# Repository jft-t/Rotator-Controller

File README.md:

# Rotator-Controller
Rotator Controller for SPID BigRAS rotator, suited for use within SatNOGS stations

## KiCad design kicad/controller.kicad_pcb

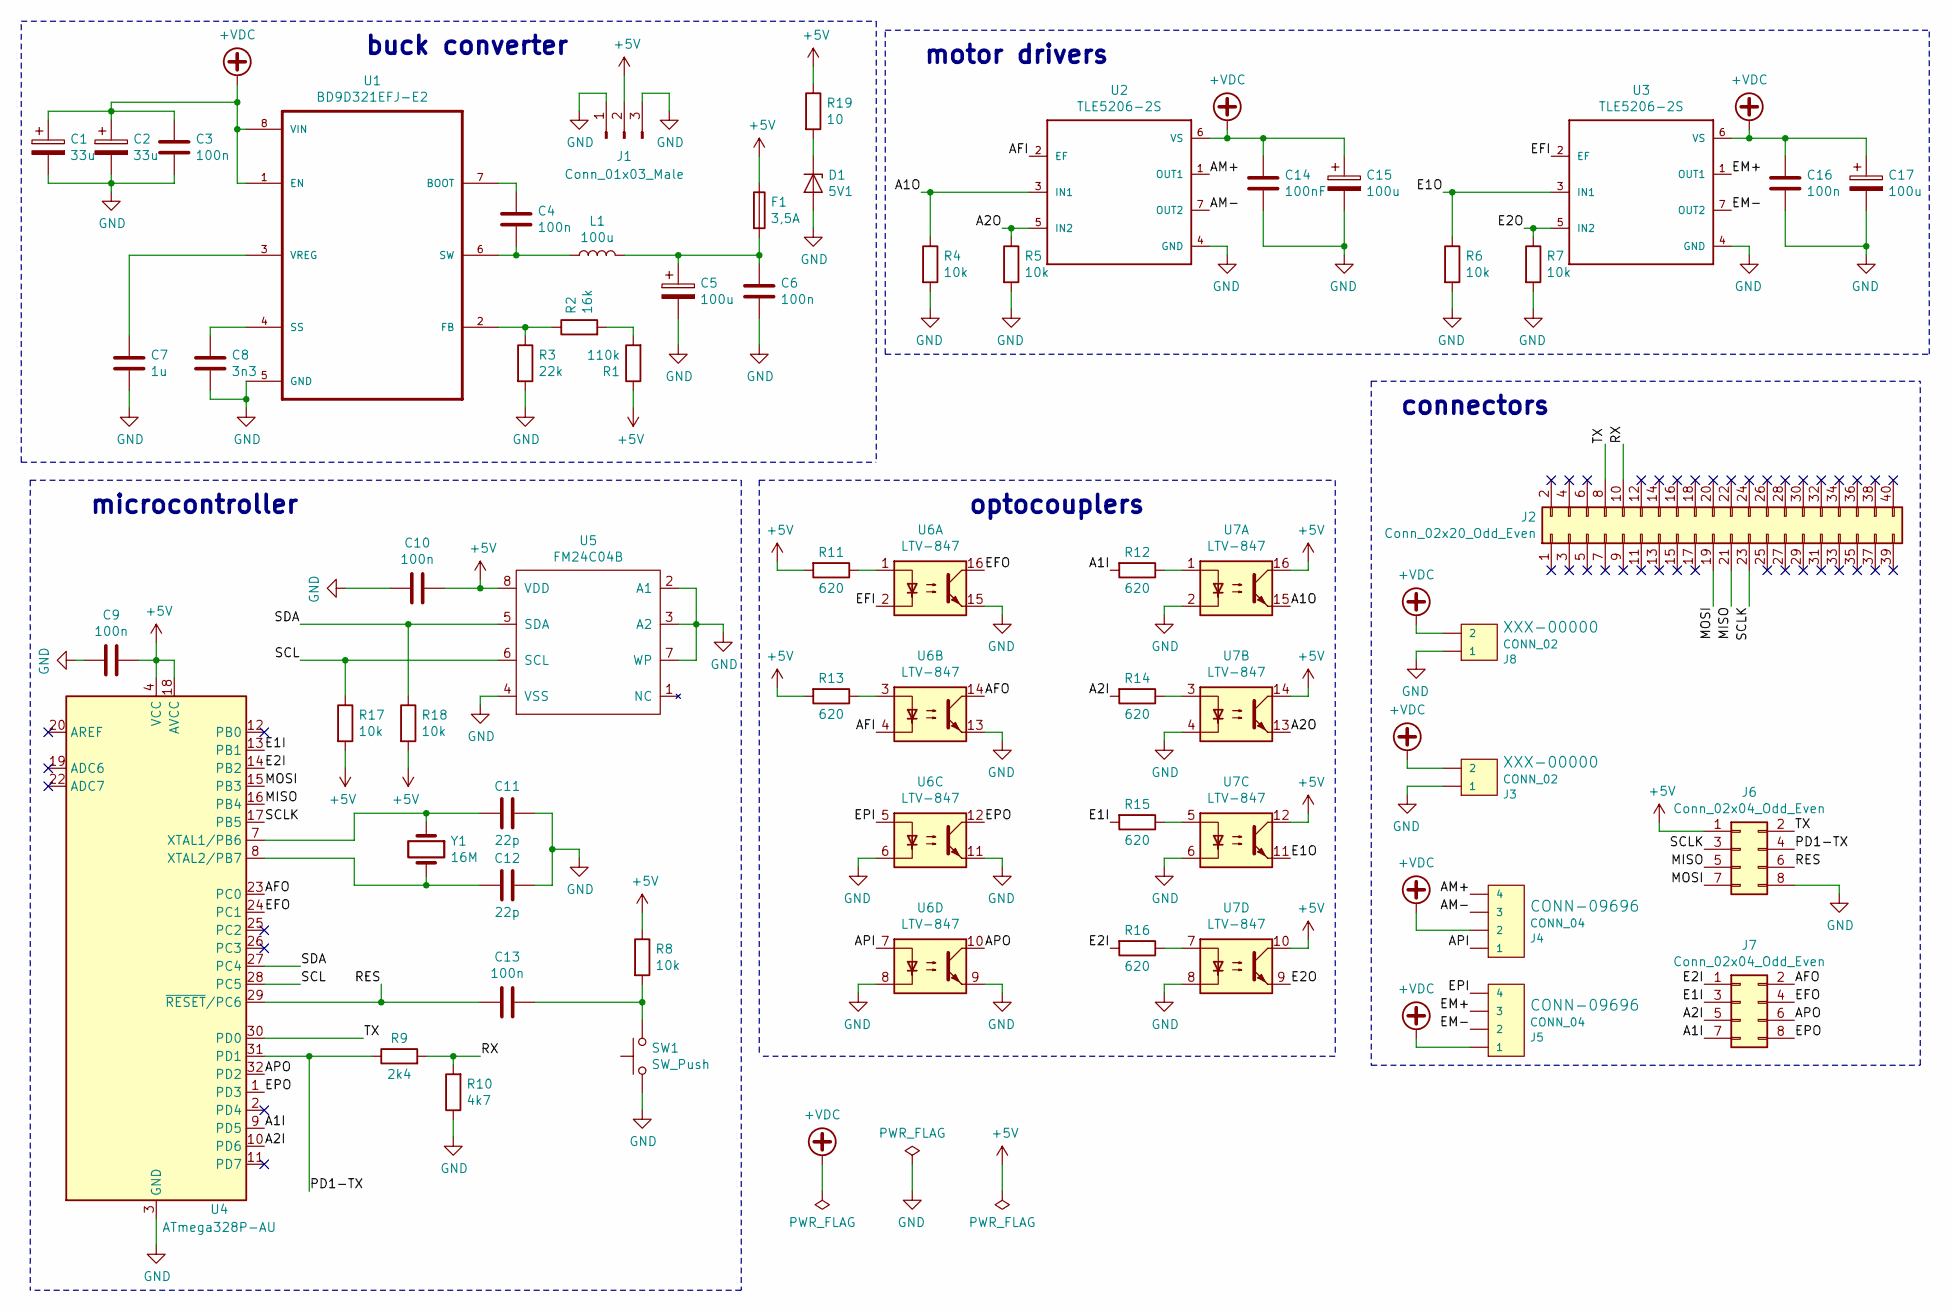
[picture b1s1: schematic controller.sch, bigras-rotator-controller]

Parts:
C1, C2: 33u; CP_EIA-7343-40_Kemet-Y_Pad2.25x2.55mm_HandSolder
C3, C4, C9, C10, C13: 100n; C_1206_3216Metric_Pad1.42x1.75mm_HandSolder
C5, C15, C17: 100u; CP_Radial_D6.3mm_P2.50mm
C6, C16: 100n; C_Rect_L4.0mm_W2.5mm_P2.50mm
C7: 1u; C_1206_3216Metric_Pad1.42x1.75mm_HandSolder
C8: 3n3; C_1206_3216Metric_Pad1.42x1.75mm_HandSolder
C11, C12: 22p; C_1206_3216Metric_Pad1.42x1.75mm_HandSolder
C14: 100nF; C_Rect_L4.0mm_W2.5mm_P2.50mm
D1: 5V1; D_SOD-123
F1: 3,5A; 154-series
J1: Conn_01x03_Male; PinHeader_1x03_P2.54mm_Vertical
J2: Conn_02x20_Odd_Even; PinHeader_2x20_P2.54mm_Vertical
J3, J8: CONN_02; CUI_TB002-500-02BE
J4, J5: CONN_04; CUI_TB002-500-04BE
J6, J7: Conn_02x04_Odd_Even; PinHeader_2x04_P2.54mm_Vertical
L1: 100u; DR127
R1: 110k; R_1206_3216Metric_Pad1.42x1.75mm_HandSolder
R2: 16k; R_1206_3216Metric_Pad1.42x1.75mm_HandSolder
R3: 22k; R_1206_3216Metric_Pad1.42x1.75mm_HandSolder
R4, R5, R6, R7, R8, R17, R18: 10k; R_1206_3216Metric_Pad1.42x1.75mm_HandSolder
R9: 2k4; R_1206_3216Metric_Pad1.42x1.75mm_HandSolder
R10: 4k7; R_1206_3216Metric_Pad1.42x1.75mm_HandSolder
R11, R12, R13, R14, R15, R16: 620; R_1206_3216Metric_Pad1.42x1.75mm_HandSolder
R19: 10; R_1206_3216Metric_Pad1.42x1.75mm_HandSolder
SW1: SW_Push; SW_SPST_EVQPE1
U1: BD9D321EFJ-E2; HSOP-8-1EP_3.9x4.9mm_P1.27mm_EP2.41x3.1mm
U2, U3: TLE5206-2S; TO-220-7_P2.54x3.7mm_StaggerEven_Lead3.8mm_Vertical
U4: ATmega328P-AU; TQFP-32_7x7mm_P0.8mm
U5: FM24C04B; SOIC-8_3.9x4.9mm_P1.27mm
U6, U7: LTV-847; DIP-16_W7.62mm
Y1: 16M; Crystal_SMD_HC49-SD

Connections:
+5V: C9.1, C10.1, F1.1, J1.2, J6.1, R1.1, R8.1, R11.2, R13.2, R17.2, R18.2, R19.1, U4.4 (VCC), U4.6 (VCC), U4.18 (AVCC), U5.8 (VDD), U7.10, U7.12, U7.14, U7.16
+VDC: C1.1, C2.1, C3.2, C14.1, C15.1, C16.1, C17.1, J3.2, J4.2, J5.1, J8.2, U1.1 (EN), U1.8 (VIN), U2.6 (VS), U3.6 (VS); also elsewhere on the board
/A1I: J7.7, R12.2, U4.9 (PD5)
/A1O: R4.1, U2.3 (IN1), U7.15
/A2I: J7.5, R14.2, U4.10 (PD6)
/A2O: R5.1, U2.5 (IN2), U7.13
/AFI: U2.2 (EF), U6.4
/AFO: J7.2, U4.23 (PC0), U6.14
/AM+: J4.4, U2.1 (OUT1)
/AM-: J4.3, U2.7 (OUT2)
/API: J4.1, U6.7
/APO: J7.6, U4.32 (PD2), U6.10
/E1I: J7.3, R15.2, U4.13 (PB1)
/E1O: R6.1, U3.3 (IN1), U7.11
/E2I: J7.1, R16.2, U4.14 (PB2)
/E2O: R7.1, U3.5 (IN2), U7.9
/EFI: U3.2 (EF), U6.2
/EFO: J7.4, U4.24 (PC1), U6.16
/EM+: J5.3, U3.1 (OUT1)
/EM-: J5.2, U3.7 (OUT2)
/EPI: J5.4, U6.5
/EPO: J7.8, U4.1 (PD3), U6.12
/MISO: J2.21, J6.5, U4.16 (PB4)
/MOSI: J2.19, J6.7, U4.15 (PB3)
/PD1-TX: J6.4, R9.1, U4.31 (PD1)
/RES: C13.2, J6.6, U4.29 (~RESET~/PC6)
/RX: J2.10, R9.2, R10.2
/SCL: R17.1, U4.28 (PC5), U5.6 (SCL)
/SCLK: J2.23, J6.3, U4.17 (PB5)
/SDA: R18.1, U4.27 (PC4), U5.5 (SDA)
/TX: J2.8, J6.2, U4.30 (PD0)
GND: C1.2, C2.2, C3.1, C5.2, C6.2, C7.2, C8.2, C9.2, C10.2, C11.1, C12.1, C14.2, C15.2, C16.2, C17.2, D1.2 (A), J1.1, J1.3, J3.1, J6.8, J8.1, R3.2, R4.2, R5.2, R6.2, R7.2, R10.1, SW1.1, U1.5 (GND), U2.4 (GND), U3.4 (GND), U4.3 (GND), U4.5 (GND), U4.21 (GND), U5.2 (A1), U5.3 (A2), U5.4 (VSS), U5.7 (WP), U6.6, U6.8, U6.9, U6.11, U6.13, U6.15, U7.2, U7.4, U7.6, U7.8; also elsewhere on the board
unnamed: C4.1, U1.7 (BOOT)
unnamed: C4.2, L1.1, U1.6 (SW)
unnamed: C5.1, C6.1, F1.2, L1.2
unnamed: C7.1, U1.3 (VREG)
unnamed: C8.1, U1.4 (SS)
unnamed: C11.2, U4.7 (XTAL1/PB6), Y1.1
unnamed: C12.2, U4.8 (XTAL2/PB7), Y1.2
unnamed: C13.1, R8.2, SW1.2
unnamed: D1.1 (K), R19.2
unnamed: R1.2, R2.2
unnamed: R2.1, R3.1, U1.2 (FB)
unnamed: R11.1, U6.1
unnamed: R12.1, U7.1
unnamed: R13.1, U6.3
unnamed: R14.1, U7.3
unnamed: R15.1, U7.5
unnamed: R16.1, U7.7

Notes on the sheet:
microcontroller
optocouplers
motor drivers
connectors
buck converter

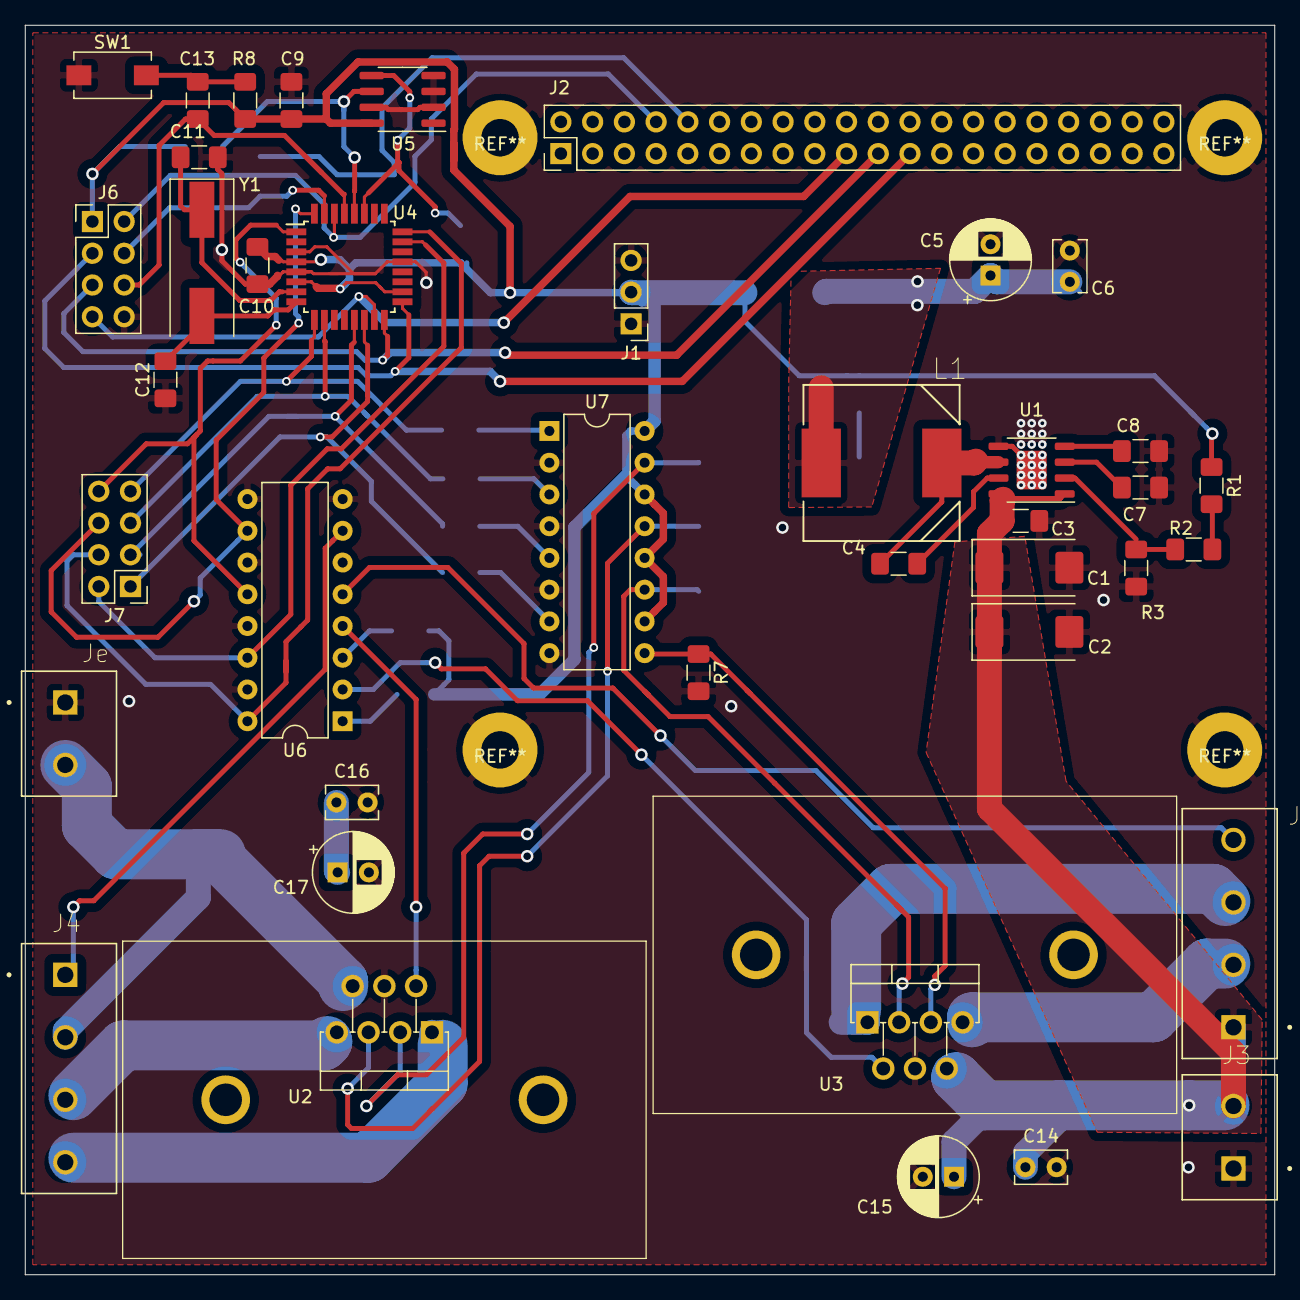
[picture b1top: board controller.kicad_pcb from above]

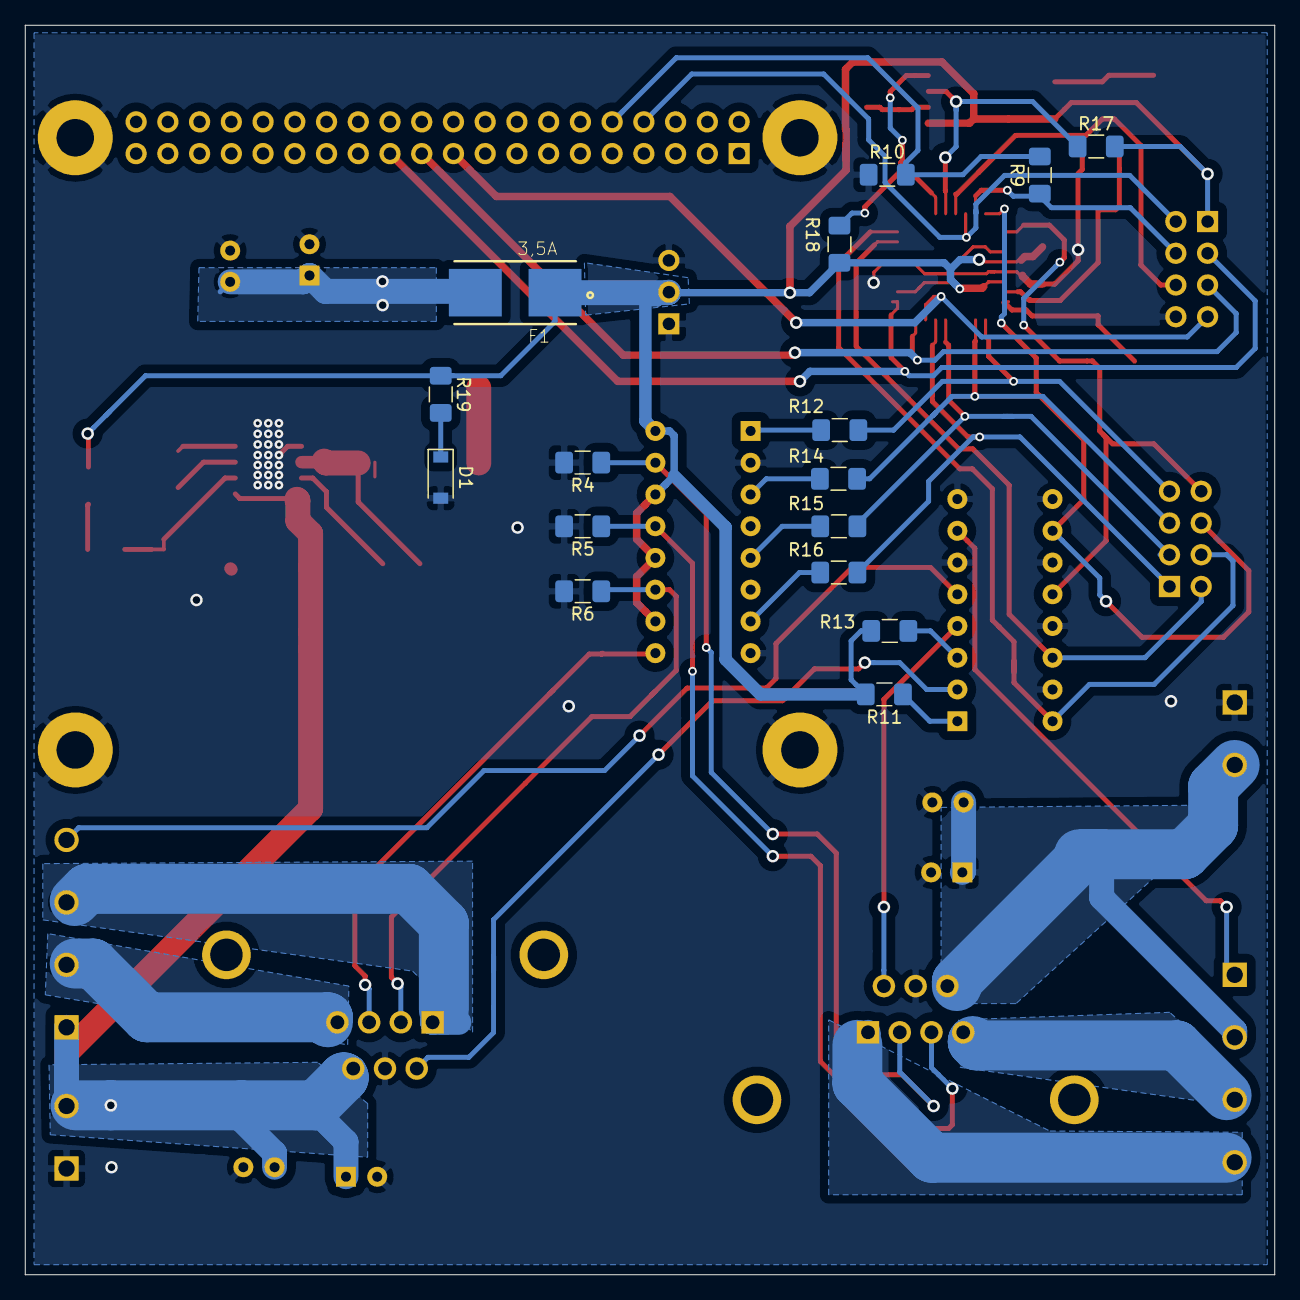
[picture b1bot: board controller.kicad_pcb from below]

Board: 2 copper layers, 100.0 x 100.0 mm, 58 parts (16 on the bottom side), 49 nets.

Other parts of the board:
H**: 65725ABEP
H**#2: 65725ABEP
Je: CONN_02; CUI_TB002-500-02BE

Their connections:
+VDC: Je.2; also elsewhere on the board
GND: Je.1; also elsewhere on the board

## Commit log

2019-08-09 Upload files, renaming
